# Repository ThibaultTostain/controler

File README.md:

# Controllers

"Controllers" est un répertoire avec tous les fichiers pour faire son propre controller quelqu'il soit.

## Présentation

Vous ne trouverez rien dans "main" que des explications générales, chaque projet ayant sa propre branche.

Dans la branche de chaque projet vous retrouverez tous les fichiers pour faire votre controller mais aussi des explications et les étapes clefs de sa conception.

## Liste des controllers

Pour l'instant on y retrouve :
- manette type XBox à fils et format brut ** (en cours) [branch : manette_xbox_fils_brut]
- ...

** format brut : les données des actionneurs ne sont pas traitées et sont données telquelles. On ne peut donc pas l'utiliser sur un ordinateur.

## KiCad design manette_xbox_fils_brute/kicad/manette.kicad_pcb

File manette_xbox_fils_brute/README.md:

# Manette Xbox à Fils au format Brute

Cette manette à pour bute majoritaire de servir dans des projets de robotique amateur. Son format de sorti n'est donc pas traité et c'est à vous de le faire.

# Etapes de conceptions

## Réalisation du modèle 3D

Pour la réalisation du modèle 3D j'ai décidé d'utiliser freecad 0.20.

### Apprendre FreeCad

Quand j'ai commencé ce projet je n'avais pas une trés grande connaissance de freecad, mais je savais que c'est sur ce logiciel que je voulais faire la partie mécanique de ce controller.

J'ai donc commencé par suivre quelques tutos de bases :
* https://www.youtube.com/watch?v=sVT9Cnz83Q4&t=862s
* https://www.youtube.com/watch?v=twRgek552j0
* https://www.youtube.com/watch?v=sXPapS0WLgk&t=11s
* https://www.youtube.com/watch?v=eWzT33H6jEg&t=9s
* https://www.youtube.com/watch?v=waAOwu4RwCM

Puis des tutos sur des parties plus précises :
* https://www.youtube.com/watch?v=yZQV8tlyq-M
* https://www.youtube.com/watch?v=rBlmyoqXRJw
* https://www.youtube.com/watch?v=MYjEPXKqwfo&t=627s
* https://www.youtube.com/watch?v=BfqCsTaO42U&t=136s
* https://www.youtube.com/watch?v=sn2aU4oMDQA
* https://www.youtube.com/watch?v=p68TArJWZ0k&t=1112s

### Réalisation d'une première version

Après ces tutos j'ai décidé de mettre en application mes connaissances pour voir ce que j'étais déjà capable de faire, et mon premier essaie est encouragant.

[Plus d'image ici](https://github.com/ThibaultTostain/controllers/tree/main/manette_xbox_fils_brute/imgs)

## Faire le schéma KiCad

### Le souhait de traiter le signal au départ et tout faire soi-même

Au départ je souhaitais faire une vraie manette xbox pour mon ordinateur. Finalement, j'ai voulu y aller étape par étape car le projet semblait trop compliqué pour l'instant. Voici quelques images de ce j'avais avant de changer d'idée

[Plus d'image ici](https://github.com/ThibaultTostain/controllers/tree/main/manette_xbox_fils_brute/imgs)

### Changement de direction : pas de traitement et on ne fait pas tout

#### Fabrication de l'empreinte du Joystick

J'ai d'abord voulu récupérer l'empreinte et le modèle 3D sur un site, mais les fichiers ne fonctionnait pas bien sur KiCad 6.0.7. Du coup j'ai décidé de refaire moi-même l'empreinte. J'ai alors suivi 2 tutos, l'un pour le schéma, l'autre pour le pcb, mais je n'ai pas encore fait la version 3D :
* https://www.youtube.com/watch?v=jlKqVysg-ts
* https://www.youtube.com/watch?v=LMgBfsWX_z0

### Réalisation d'une première version

J'ai donc décidé de réaliser à nouveau un pcb mais cette fois avec un joystick déjà fabriqué et un signal de sorti "brut".

[Plus d'image ici](https://github.com/ThibaultTostain/controllers/tree/main/manette_xbox_fils_brute/imgs)

Et même si j'avais déjà posé les contraintes de dimensions sur l'écart entre les élements, le pas entre les boutons, je n'avais pas prété attention dans cette version aux dimensions externes. Ce qui ma fait réaliser une carte bien trop grande pour rentrer dans une manette.

### Optimisation des placements pour tout faire rentrer dans un format conventionnel

J'ai donc décidé de réarenger les composants pour avoir des dimensions plus petite. Et avec succés, j'ai réalisé une carte qui rentre dans un boitier de manete sans problème, et cela en gardant la contrainte de pouvoir fabriquer cette pièce facilement chez soi, et donc sans composants CMS.
On est passé de 106x74mm à 100x53mm, soit une réduction de 32% de la surface.

[Plus d'image ici](https://github.com/ThibaultTostain/controllers/tree/main/manette_xbox_fils_brute/imgs)

### Prochaines étapes : mettre une extension de ports Arduino intégré & un écran tout en restant dans les tailles limites

Pour réduire le nombre de pins utilisés par la manette, j'aimerai ajouté une extension de ports arduino directement dans la manette pour n'utiliser que 2 pins Arduino mais tout de même garder les pins lisibles séparement par l'Arduino.

Voici mes premières ressources :
- https://esphome.io/cookbook/arduino_port_extender.html
- https://thecustomizewindows.com/2017/10/increase-number-digital-pins-arduino/

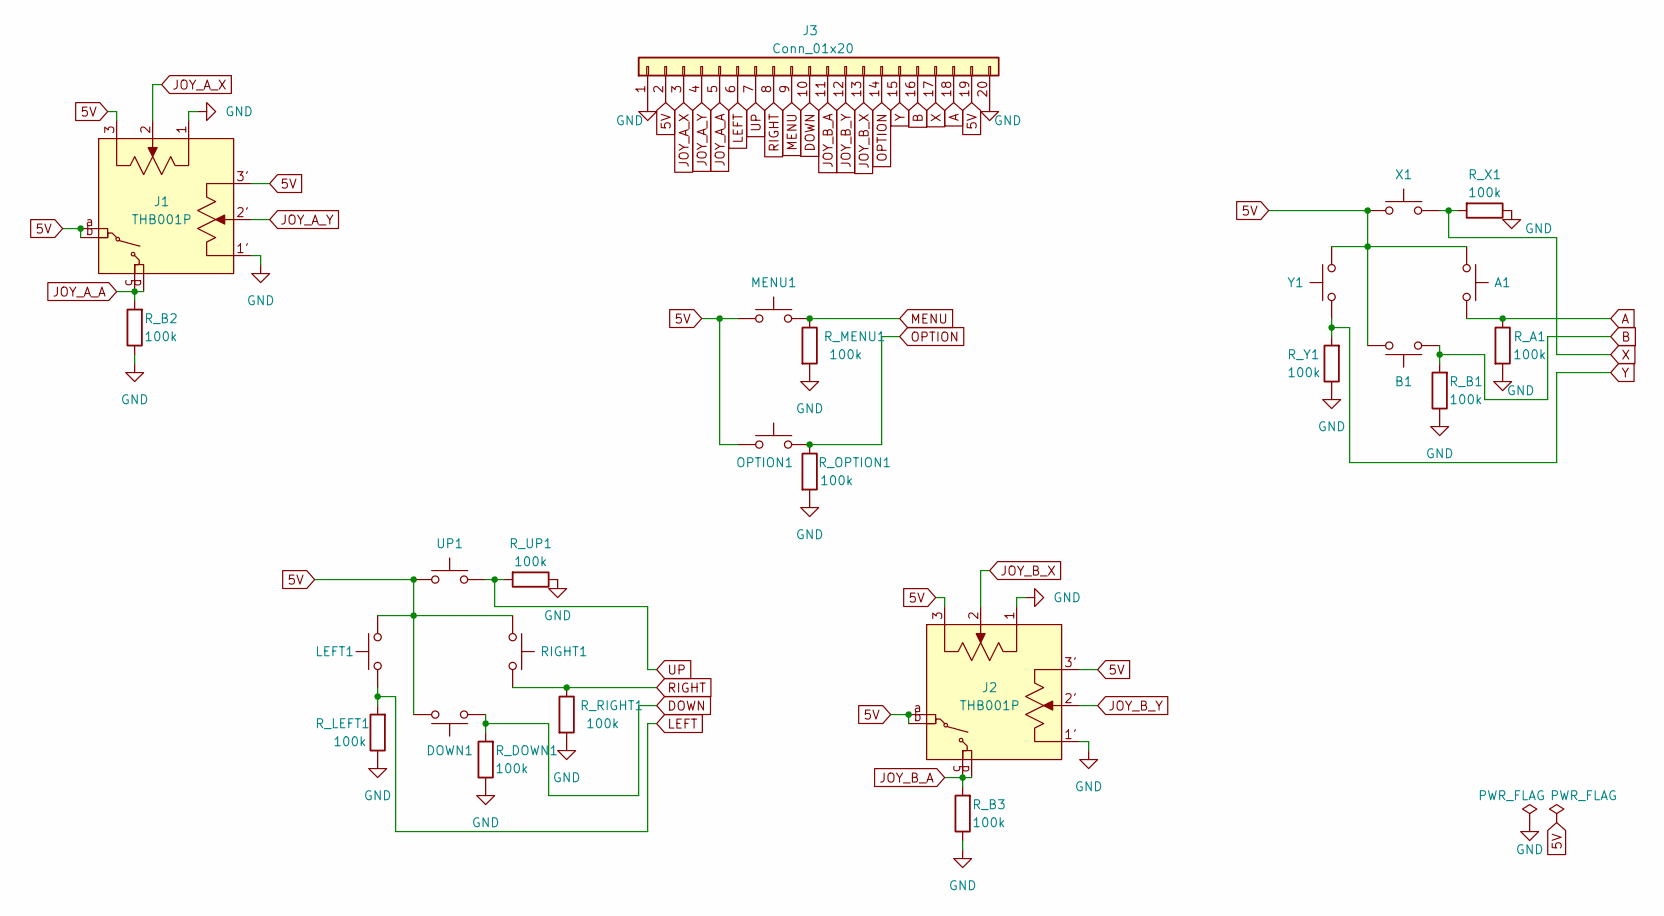
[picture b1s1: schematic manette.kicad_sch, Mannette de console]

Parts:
A1: SW_Push; SW_PUSH_6mm_H9.5mm
B1: SW_Push; SW_PUSH_6mm_H9.5mm
DOWN1: SW_Push; SW_PUSH_6mm_H9.5mm
J1, J2: THB001P; Joystick_THB001P
J3: Conn_01x20; JST_XH_B20B-XH-A_1x20_P2.50mm_Vertical
LEFT1: SW_Push; SW_PUSH_6mm_H9.5mm
MENU1: SW_Push; SW_PUSH_6mm_H9.5mm
OPTION1: SW_Push; SW_PUSH_6mm_H9.5mm
RIGHT1: SW_Push; SW_PUSH_6mm_H9.5mm
R_A1: 100k; R_Axial_DIN0411_L9.9mm_D3.6mm_P15.24mm_Horizontal
R_B1, R_B2, R_B3: 100k; R_Axial_DIN0411_L9.9mm_D3.6mm_P15.24mm_Horizontal
R_DOWN1: 100k; R_Axial_DIN0411_L9.9mm_D3.6mm_P15.24mm_Horizontal
R_LEFT1: 100k; R_Axial_DIN0411_L9.9mm_D3.6mm_P15.24mm_Horizontal
R_MENU1: 100k; R_Axial_DIN0411_L9.9mm_D3.6mm_P15.24mm_Horizontal
R_OPTION1: 100k; R_Axial_DIN0411_L9.9mm_D3.6mm_P15.24mm_Horizontal
R_RIGHT1: 100k; R_Axial_DIN0411_L9.9mm_D3.6mm_P15.24mm_Horizontal
R_UP1: 100k; R_Axial_DIN0411_L9.9mm_D3.6mm_P15.24mm_Horizontal
R_X1: 100k; R_Axial_DIN0411_L9.9mm_D3.6mm_P15.24mm_Horizontal
R_Y1: 100k; R_Axial_DIN0411_L9.9mm_D3.6mm_P15.24mm_Horizontal
UP1: SW_Push; SW_PUSH_6mm_H9.5mm
X1: SW_Push; SW_PUSH_6mm_H9.5mm
Y1: SW_Push; SW_PUSH_6mm_H9.5mm

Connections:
5V: A1.1, B1.2, DOWN1.2, J1.3, J1.3', J1.a, J1.b, J2.3, J2.3', J2.a, J2.b, J3.2, J3.19, LEFT1.2, MENU1.1, OPTION1.1, RIGHT1.1, UP1.1, X1.1, Y1.2
A: A1.2, J3.18, R_A1.1
B: B1.1, J3.16, R_B1.2
DOWN: DOWN1.1, J3.10, R_DOWN1.2
GND: J1.1, J1.1', J2.1, J2.1', J3.1, J3.20, R_A1.2, R_B1.1, R_B2.1, R_B3.1, R_DOWN1.1, R_LEFT1.1, R_MENU1.2, R_OPTION1.2, R_RIGHT1.2, R_UP1.1, R_X1.1, R_Y1.1
JOY_A_A: J1.c, J1.d, J3.5, R_B2.2
JOY_A_X: J1.2, J3.3
JOY_A_Y: J1.2', J3.4
JOY_B_A: J2.c, J2.d, J3.11, R_B3.2
JOY_B_X: J2.2, J3.13
JOY_B_Y: J2.2', J3.12
LEFT: J3.6, LEFT1.1, R_LEFT1.2
MENU: J3.9, MENU1.2, R_MENU1.1
OPTION: J3.14, OPTION1.2, R_OPTION1.1
RIGHT: J3.8, RIGHT1.2, R_RIGHT1.1
UP: J3.7, R_UP1.2, UP1.2
X: J3.17, R_X1.2, X1.2
Y: J3.15, R_Y1.2, Y1.1

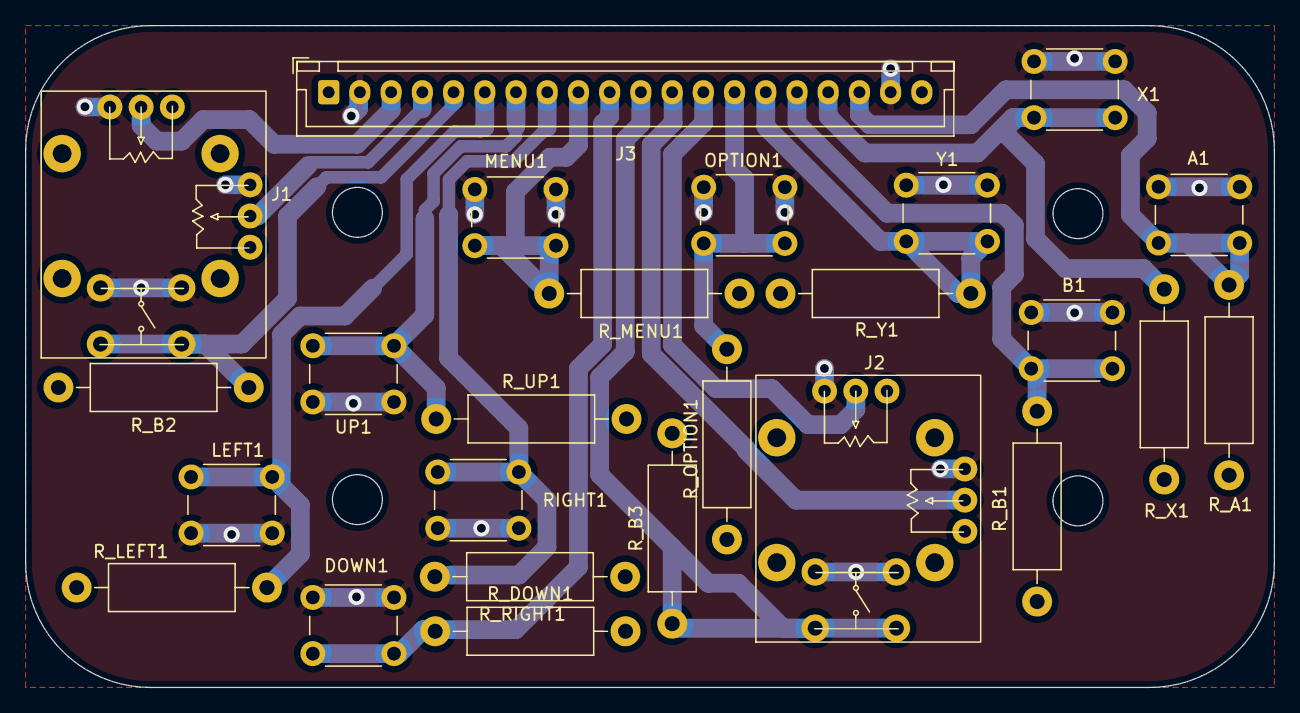
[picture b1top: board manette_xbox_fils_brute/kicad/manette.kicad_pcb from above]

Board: 2 copper layers, 100.0 x 53.0 mm, 25 parts (0 on the bottom side), 18 nets.

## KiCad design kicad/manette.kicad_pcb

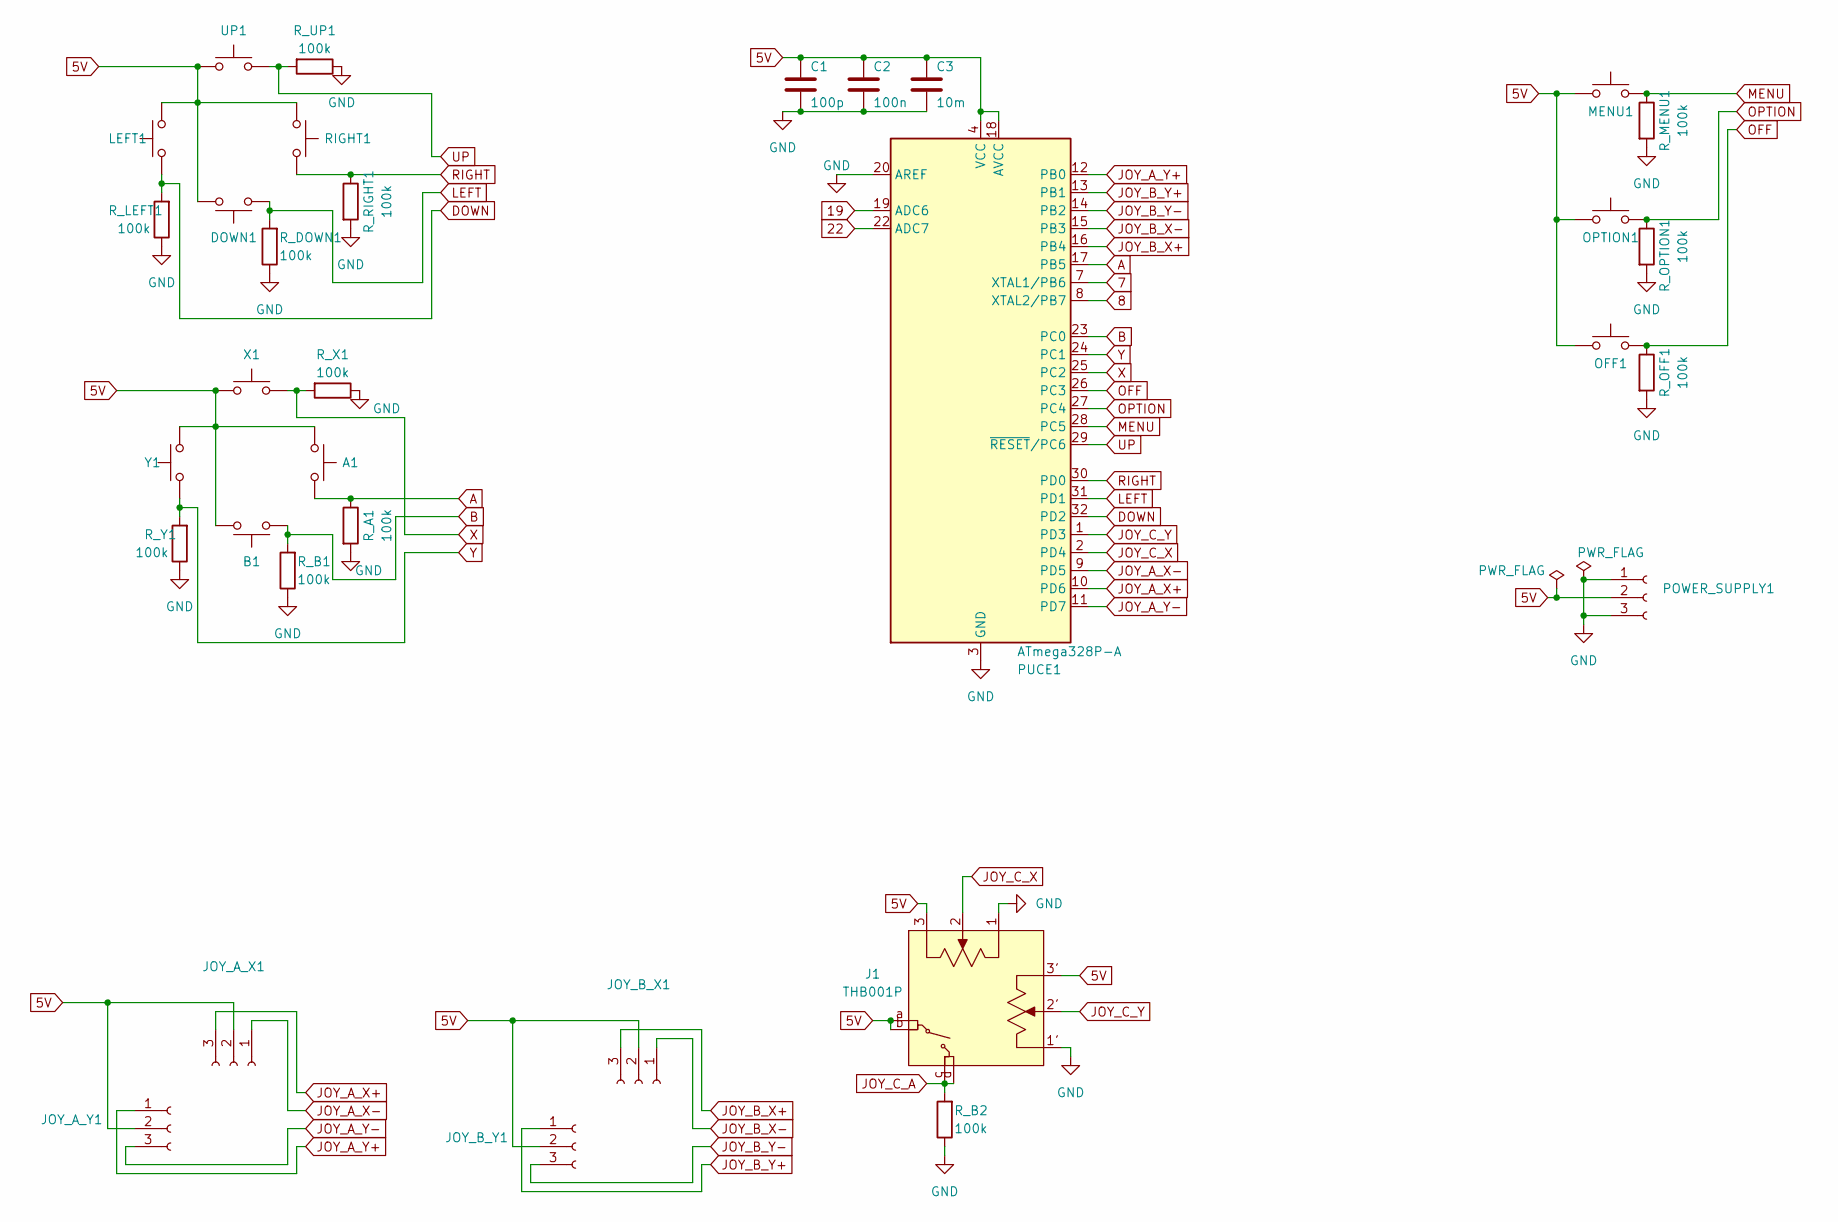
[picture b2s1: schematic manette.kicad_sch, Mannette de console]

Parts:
A1: SW_Push; SW_PUSH_6mm_H9.5mm
B1: SW_Push; SW_PUSH_6mm_H9.5mm
C1: 100p; CP_Radial_D5.0mm_P2.50mm
C2: 100n; CP_Radial_D5.0mm_P2.50mm
C3: 10m; CP_Radial_D5.0mm_P2.50mm
DOWN1: SW_Push; SW_PUSH_6mm_H9.5mm
J1: THB001P; Joystick_THB001P
JOY_A_X1: Conn_01x03_Female; SolderWire-0.15sqmm_1x03_P4mm_D0.5mm_OD1.5mm
JOY_A_Y1: Conn_01x03_Female; SolderWire-0.15sqmm_1x03_P4mm_D0.5mm_OD1.5mm
JOY_B_X1: Conn_01x03_Female; SolderWire-0.15sqmm_1x03_P4mm_D0.5mm_OD1.5mm
JOY_B_Y1: Conn_01x03_Female; SolderWire-0.15sqmm_1x03_P4mm_D0.5mm_OD1.5mm
LEFT1: SW_Push; SW_PUSH_6mm_H9.5mm
MENU1: SW_Push; SW_PUSH_6mm_H9.5mm
OFF1: SW_Push; SW_PUSH_6mm_H9.5mm
OPTION1: SW_Push; SW_PUSH_6mm_H9.5mm
POWER_SUPPLY1: Conn_01x03_Female; SolderWire-0.15sqmm_1x03_P4mm_D0.5mm_OD1.5mm
PUCE1: ATmega328P-A; TQFP-32_7x7mm_P0.8mm
RIGHT1: SW_Push; SW_PUSH_6mm_H9.5mm
R_A1: 100k; R_Axial_DIN0411_L9.9mm_D3.6mm_P15.24mm_Horizontal
R_B1, R_B2: 100k; R_Axial_DIN0411_L9.9mm_D3.6mm_P15.24mm_Horizontal
R_DOWN1: 100k; R_Axial_DIN0411_L9.9mm_D3.6mm_P15.24mm_Horizontal
R_LEFT1: 100k; R_Axial_DIN0411_L9.9mm_D3.6mm_P15.24mm_Horizontal
R_MENU1: 100k; R_Axial_DIN0411_L9.9mm_D3.6mm_P15.24mm_Horizontal
R_OFF1: 100k; R_Axial_DIN0411_L9.9mm_D3.6mm_P15.24mm_Horizontal
R_OPTION1: 100k; R_Axial_DIN0411_L9.9mm_D3.6mm_P15.24mm_Horizontal
R_RIGHT1: 100k; R_Axial_DIN0411_L9.9mm_D3.6mm_P15.24mm_Horizontal
R_UP1: 100k; R_Axial_DIN0411_L9.9mm_D3.6mm_P15.24mm_Horizontal
R_X1: 100k; R_Axial_DIN0411_L9.9mm_D3.6mm_P15.24mm_Horizontal
R_Y1: 100k; R_Axial_DIN0411_L9.9mm_D3.6mm_P15.24mm_Horizontal
UP1: SW_Push; SW_PUSH_6mm_H9.5mm
X1: SW_Push; SW_PUSH_6mm_H9.5mm
Y1: SW_Push; SW_PUSH_6mm_H9.5mm

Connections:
5V: A1.1, B1.2, C1.1, C2.1, C3.1, DOWN1.2, J1.3, J1.3', J1.a, J1.b, JOY_A_X1.2, JOY_A_Y1.2, JOY_B_X1.2, JOY_B_Y1.2, LEFT1.2, MENU1.1, OFF1.1, OPTION1.1, POWER_SUPPLY1.2, PUCE1.4 (VCC), PUCE1.6 (VCC), PUCE1.18 (AVCC), RIGHT1.1, UP1.1, X1.1, Y1.2
7: PUCE1.7 (XTAL1/PB6)
8: PUCE1.8 (XTAL2/PB7)
19: PUCE1.19 (ADC6)
22: PUCE1.22 (ADC7)
A: A1.2, PUCE1.17 (PB5), R_A1.1
B: B1.1, PUCE1.23 (PC0), R_B1.2
DOWN: LEFT1.1, PUCE1.32 (PD2), R_LEFT1.2
GND: C1.2, C2.2, C3.2, J1.1, J1.1', POWER_SUPPLY1.1, POWER_SUPPLY1.3, PUCE1.3 (GND), PUCE1.5 (GND), PUCE1.20 (AREF), PUCE1.21 (GND), R_A1.2, R_B1.1, R_B2.1, R_DOWN1.1, R_LEFT1.1, R_MENU1.2, R_OFF1.2, R_OPTION1.2, R_RIGHT1.2, R_UP1.1, R_X1.1, R_Y1.1
JOY_A_X+: JOY_A_X1.3, PUCE1.10 (PD6)
JOY_A_X-: JOY_A_X1.1, PUCE1.9 (PD5)
JOY_A_Y+: JOY_A_Y1.1, PUCE1.12 (PB0)
JOY_A_Y-: JOY_A_Y1.3, PUCE1.11 (PD7)
JOY_B_X+: JOY_B_X1.3, PUCE1.16 (PB4)
JOY_B_X-: JOY_B_X1.1, PUCE1.15 (PB3)
JOY_B_Y+: JOY_B_Y1.1, PUCE1.13 (PB1)
JOY_B_Y-: JOY_B_Y1.3, PUCE1.14 (PB2)
JOY_C_A: J1.c, J1.d, R_B2.2
JOY_C_X: J1.2, PUCE1.2 (PD4)
JOY_C_Y: J1.2', PUCE1.1 (PD3)
LEFT: DOWN1.1, PUCE1.31 (PD1), R_DOWN1.2
MENU: MENU1.2, PUCE1.28 (PC5), R_MENU1.1
OFF: OFF1.2, PUCE1.26 (PC3), R_OFF1.1
OPTION: OPTION1.2, PUCE1.27 (PC4), R_OPTION1.1
RIGHT: PUCE1.30 (PD0), RIGHT1.2, R_RIGHT1.1
UP: PUCE1.29 (~RESET/PC6), R_UP1.2, UP1.2
X: PUCE1.25 (PC2), R_X1.2, X1.2
Y: PUCE1.24 (PC1), R_Y1.2, Y1.1

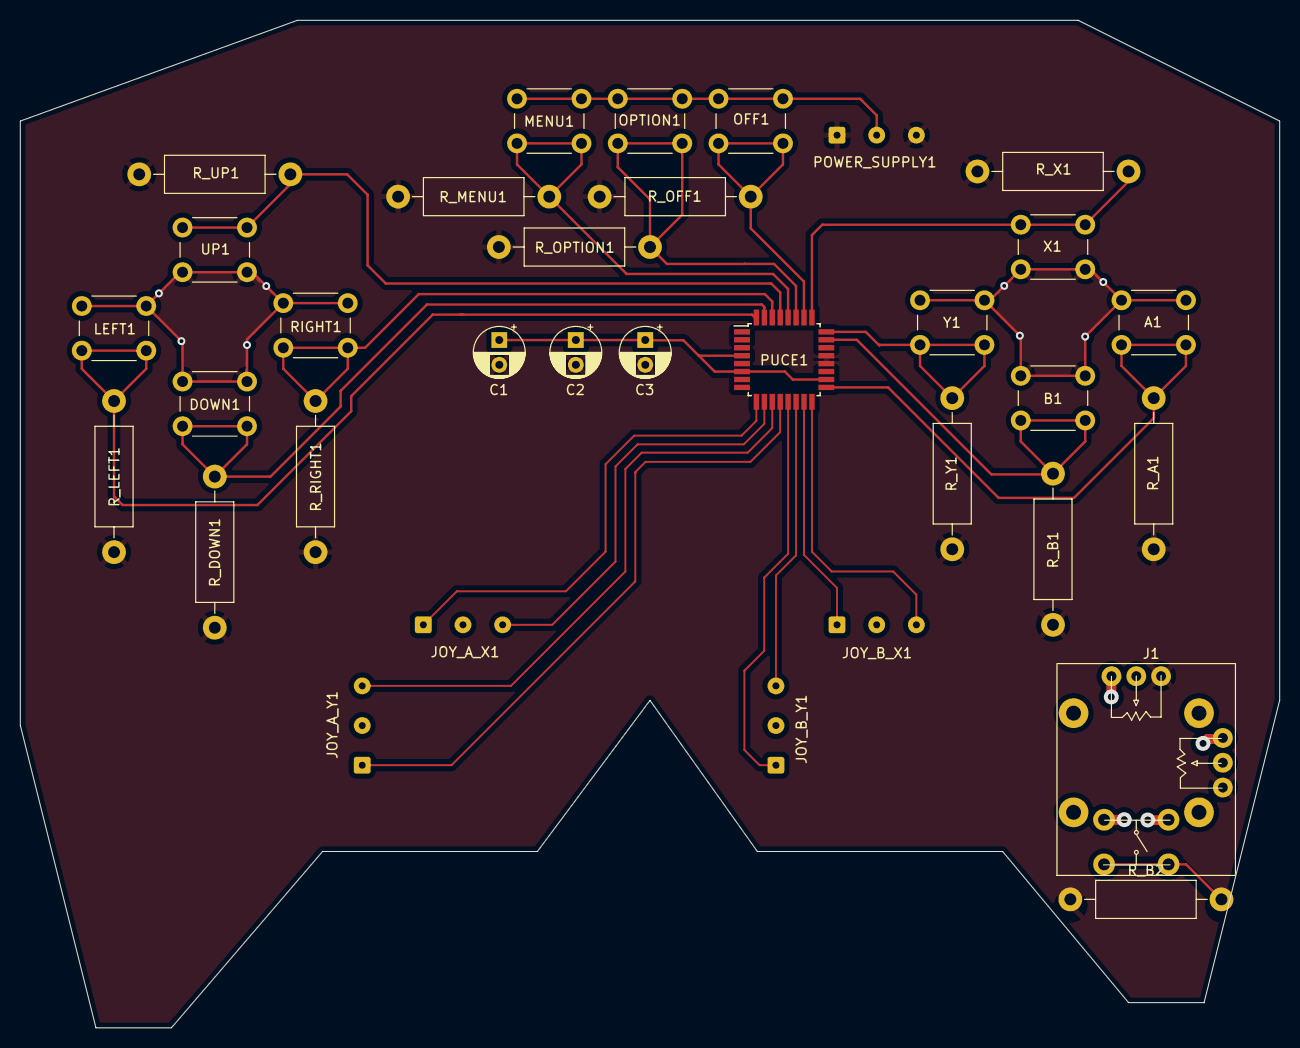
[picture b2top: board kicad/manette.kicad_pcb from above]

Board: 2 copper layers, 127.0 x 101.6 mm, 33 parts (0 on the bottom side), 24 nets.

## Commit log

2022-10-23 add kicad project
2022-10-25 what is it ?
2022-10-29 ajout d'un joystick achetable
2022-10-29 changement méthodologie
2022-10-29 ajouts imgs ancienne version
2022-10-29 ajout imgs ancienne version
2022-10-29 changement en version brut + ajout joystick générique
2022-10-30 add sources of dimensions
2022-10-31 test - apprentissage github A
2022-10-31 redimensionnement de la carte
2022-10-31 nettoyage d'un fil mal placé
2022-10-31 déplace un cercle
2022-10-31 correction fils superposé
2022-11-02 ajout modélisation manette 3d
2022-11-02 mise à jour de l'avancé sur le projet
2022-11-05 correction erreur & changement forme et trous pcb
2022-11-20 je ne sais pas ce que c'est
2022-12-14 ajouts de la partie "prochaine étape"
2022-12-14 màj "prochaines étapes"
